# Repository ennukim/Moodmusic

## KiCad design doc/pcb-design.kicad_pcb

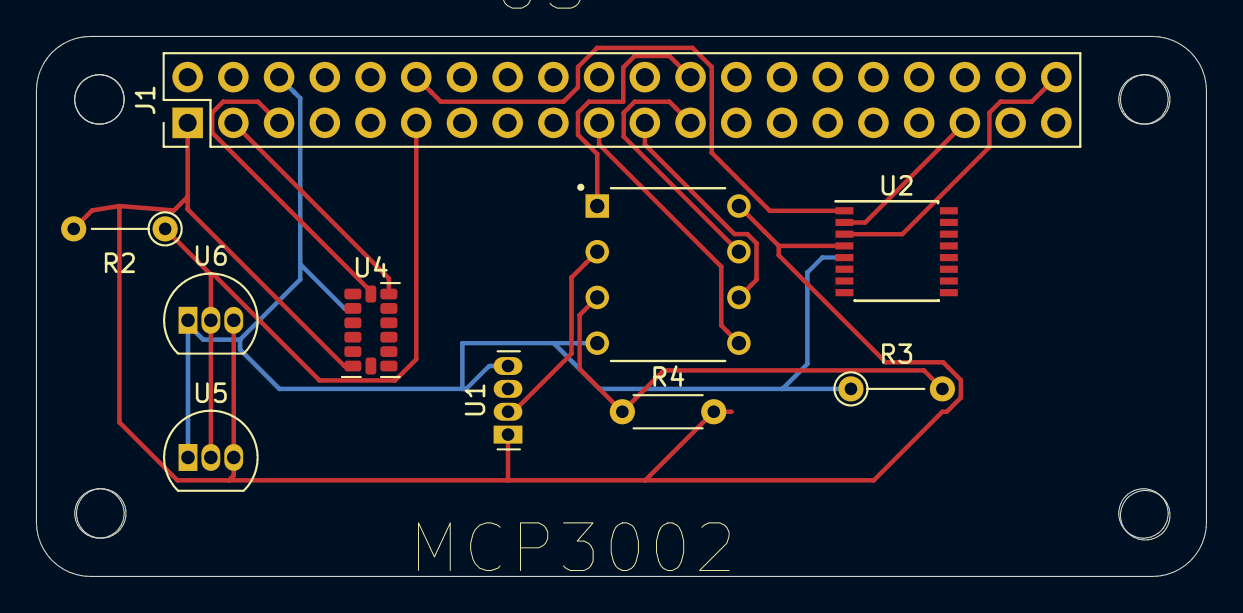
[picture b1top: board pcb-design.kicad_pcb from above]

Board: 2 copper layers, 65.0 x 30.0 mm, 10 parts (0 on the bottom side), 14 nets.

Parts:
J1: Conn_02x20_Odd_Even; PinHeader_2x20_P2.54mm_Vertical
R2: 4.7k; R_Axial_DIN0204_L3.6mm_D1.6mm_P5.08mm_Vertical
R3: 470; R_Axial_DIN0204_L3.6mm_D1.6mm_P5.08mm_Vertical
R4: R_PHOTO; R_Axial_DIN0204_L3.6mm_D1.6mm_P5.08mm_Horizontal
U1: A1363xKTTN-1; Allegro_SIP-4
U2: UDA1334ATS; SSOP-16_4.4x5.2mm_P0.65mm
U3: MCP3002; DIP787W46P254L927H533Q8
U4: ADXL343; LGA-14_3x5mm_P0.8mm_LayoutBorder1x6y
U5, U6: DS18B20; TO-92_Inline

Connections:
/3.3V: J1.1, R2.2, R4.2, U1.1, U2.4, U3.8, U4.6, U5.3, U6.3
/CH0: U1.2, U3.2
/CH1: R3.2, R4.1, U3.3
/GND: J1.6, R3.1, U1.4, U2.5, U3.4, U4.2, U4.4, U4.5, U5.1, U6.1
/GPIO2: J1.3, U4.13
/GPIO3: J1.5, U4.14
/GPIO8: J1.24, U3.1
/GPIO9: J1.21, U3.6
/GPIO10: J1.19, U3.5
/GPIO11: J1.23, U3.7
/GPIO17: J1.11, R2.1, U5.2, U6.2
/GPIO18: J1.12, U2.1
/GPIO19: J1.35, U2.2
/GPIO21: J1.40, U2.3

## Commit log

2020-10-31 Senior Design Project

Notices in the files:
doc/pcb-design.kicad_pcb:
License: MIT - Copyright 2018 StudioPieters®
